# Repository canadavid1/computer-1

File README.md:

# computer-1
A repository containing documentation, specifications, images and code for my processor built out of discrete 2N7002  transistors.

## Motivation
This project is mostly intended as a learning experience. 

## Directories
### Kicad
Kicad files for all the PCBs used in the project.

NOTICE: some of these have some flaws. Do not rely on these working.
### Assembly
Assorted assembly programs, and the corresponding compiler.
### Emulator
Different levels of emulator for the system.
### Ideas
Ideas for further improvement or additions to the system.

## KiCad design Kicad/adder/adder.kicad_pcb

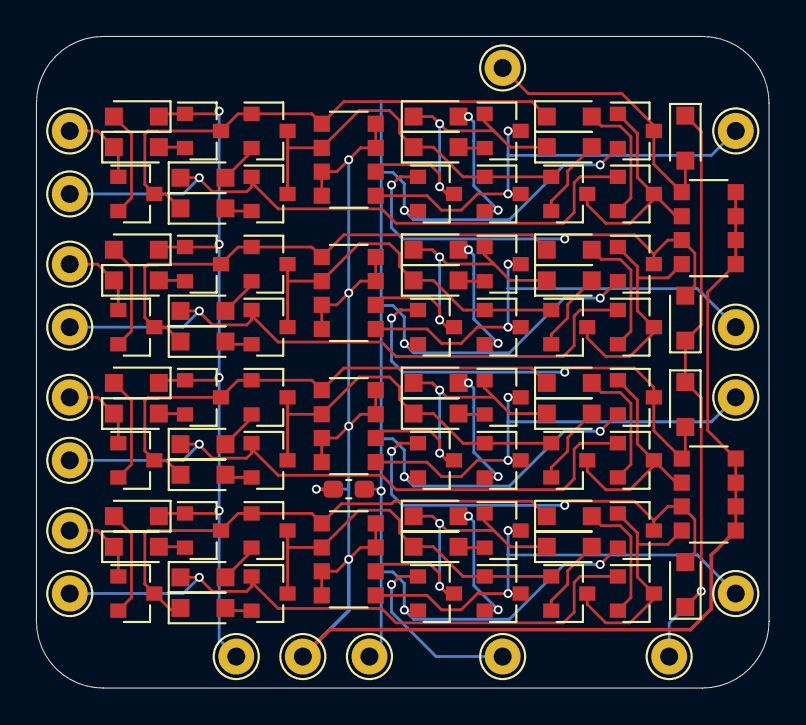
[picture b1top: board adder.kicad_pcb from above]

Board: 2 copper layers, 40.7 x 36.2 mm, 101 parts (0 on the bottom side), 69 nets.

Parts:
C0: C; C_0603_1608Metric_Pad1.08x0.95mm_HandSolder
D0, D1, D2, D3, D4, D5, D6, D7, D8, D201, D202, D203, D204, D205, D206, D207, D208, D209, D301, D302, D303, D304, D305, D306, D307, D308, D309, D401, D402, D403, D404, D405, D406, D407, D408, D409: D; D_SOD-323_HandSoldering
Q0, Q1, Q2, Q3, Q4, Q5, Q6, Q7, Q8, Q9, Q201, Q202, Q203, Q204, Q205, Q206, Q207, Q208, Q209, Q210, Q301, Q302, Q303, Q304, Q305, Q306, Q307, Q308, Q309, Q310, Q401, Q402, Q403, Q404, Q405, Q406, Q407, Q408, Q409, Q410: 2N7002; SOT-23
RN0, RN1, RN2, RN201, RN301, RN401: R_Pack04; R_Array_Convex_4x1206
TP0, TP1, TP2, TP3, TP4, TP5, TP6, TP7, TP8, TP201, TP202, TP203, TP301, TP302, TP303, TP401, TP402, TP403: Pin_D1.0mm_L10.0mm

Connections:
/1/A: D209.1, Q208.1, TP202.1
/1/B: D203.1, Q202.1, Q207.1, TP201.1
/1/SUM: Q204.3, Q205.3, RN201.5, TP203.1
/1/nA': D202.1, D207.1, Q203.1, Q208.3, Q209.3, RN201.1
/1/nCi: D205.1, D206.1, Q204.1, Q210.3, RN201.6
/1/nCo: Q201.1, Q206.3, Q207.3, RN1.2
/1/~A^B: D204.1, Q202.3, Q203.3, Q205.1, Q206.1, RN201.2
/2/A: D309.1, Q308.1, TP302.1
/2/B: D303.1, Q302.1, Q307.1, TP301.1
/2/Ci: D201.2, Q201.3, Q310.1, RN1.1
/2/SUM: Q304.3, Q305.3, RN301.5, TP303.1
/2/nA': D302.1, D307.1, Q303.1, Q308.3, Q309.3, RN301.1
/2/nCi: D305.1, D306.1, Q304.1, Q310.3, RN301.6
/2/nCo: Q301.1, Q306.3, Q307.3, RN2.4
/2/~A^B: D304.1, Q302.3, Q303.3, Q305.1, Q306.1, RN301.2
/3/A: D409.1, Q408.1, TP402.1
/3/B: D403.1, Q402.1, Q407.1, TP401.1
/3/Ci: D301.2, Q301.3, Q410.1, RN2.3
/3/Co: D401.2, Q401.3, RN2.1, TP5.1
/3/SUM: Q404.3, Q405.3, RN401.5, TP403.1
/3/nA': D402.1, D407.1, Q403.1, Q408.3, Q409.3, RN401.1
/3/nCi: D405.1, D406.1, Q404.1, Q410.3, RN401.6
/3/nCo: Q401.1, Q406.3, Q407.3, RN2.2
/3/~A^B: D404.1, Q402.3, Q403.3, Q405.1, Q406.1, RN401.2
/A: D8.1, Q7.1, TP2.1
/B: D2.1, Q1.1, Q6.1, TP1.1
/Ci: Q9.1, TP4.1
/Co: D0.2, Q0.3, Q210.1, RN1.3
/SUM: Q3.3, Q4.3, RN0.5, TP3.1
/nA': D1.1, D6.1, Q2.1, Q7.3, Q8.3, RN0.1
/nCi: D4.1, D5.1, Q3.1, Q9.3, RN0.6
/nCo: Q0.1, Q5.3, Q6.3, RN1.4
/~A^B: D3.1, Q1.3, Q2.3, Q4.1, Q5.1, RN0.2
CLRC: D0.1, D201.1, D301.1, D401.1, TP0.1
GND: C0.2, Q0.2, Q9.2, Q201.2, Q210.2, Q301.2, Q310.2, Q401.2, Q410.2, TP8.1
unnamed: D1.2, Q1.2
unnamed: D2.2, Q2.2
unnamed: D3.2, Q3.2
unnamed: D4.2, Q4.2
unnamed: D5.2, Q5.2
unnamed: D6.2, Q6.2
unnamed: D7.2, Q7.2
unnamed: D8.2, Q8.2
unnamed: D202.2, Q202.2
unnamed: D203.2, Q203.2
unnamed: D204.2, Q204.2
unnamed: D205.2, Q205.2
unnamed: D206.2, Q206.2
unnamed: D207.2, Q207.2
unnamed: D208.2, Q208.2
unnamed: D209.2, Q209.2
unnamed: D302.2, Q302.2
unnamed: D303.2, Q303.2
unnamed: D304.2, Q304.2
unnamed: D305.2, Q305.2
unnamed: D306.2, Q306.2
unnamed: D307.2, Q307.2
unnamed: D308.2, Q308.2
unnamed: D309.2, Q309.2
unnamed: D402.2, Q402.2
unnamed: D403.2, Q403.2
unnamed: D404.2, Q404.2
unnamed: D405.2, Q405.2
unnamed: D406.2, Q406.2
unnamed: D407.2, Q407.2
unnamed: D408.2, Q408.2
unnamed: D409.2, Q409.2
VCC: C0.1, RN0.3, RN0.4, RN0.7, RN0.8, RN1.5, RN1.6, RN1.7, RN1.8, RN2.5, RN2.6, RN2.7, RN2.8, RN201.3, RN201.4, RN201.7, RN201.8, RN301.3, RN301.4, RN301.7, RN301.8, RN401.3, RN401.4, RN401.7, RN401.8, TP7.1
~add: D7.1, D208.1, D308.1, D408.1, Q8.1, Q209.1, Q309.1, Q409.1, TP6.1

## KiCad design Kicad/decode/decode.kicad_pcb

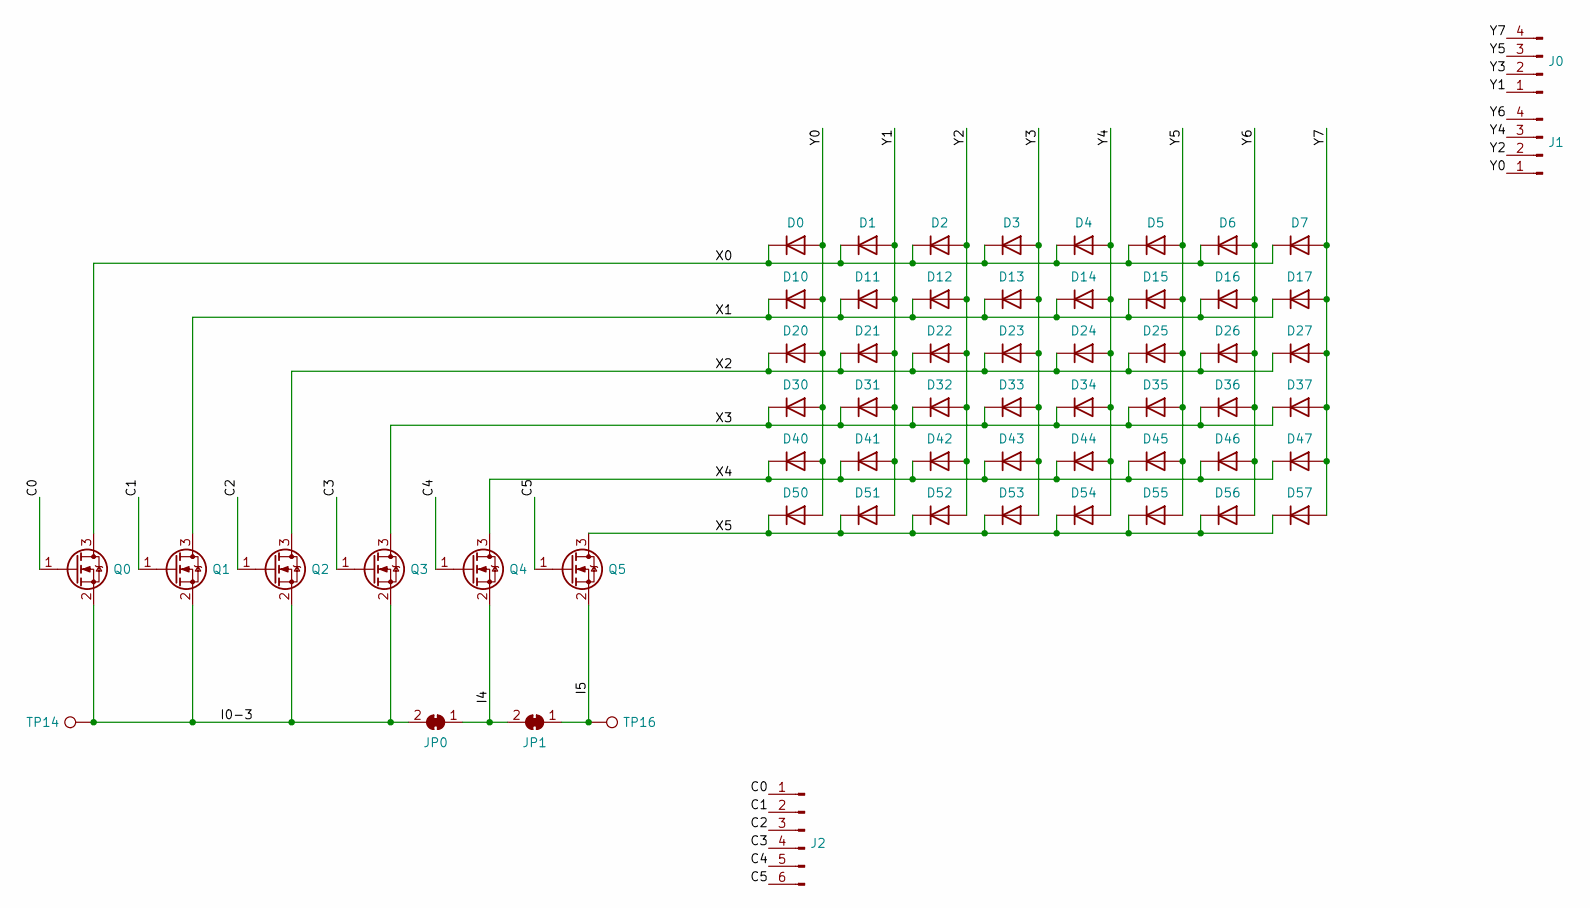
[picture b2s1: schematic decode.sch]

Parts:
D0, D1, D2, D3, D4, D5, D6, D7, D10, D11, D12, D13, D14, D15, D16, D17, D20, D21, D22, D23, D24, D25, D26, D27, D30, D31, D32, D33, D34, D35, D36, D37, D40, D41, D42, D43, D44, D45, D46, D47, D50, D51, D52, D53, D54, D55, D56, D57: D; D_SOD-323_HandSoldering
J0, J1: Conn_01x04_Male; PinHeader_1x04_P2.54mm_Vertical
J2: Conn_01x06_Male; PinHeader_1x06_P2.54mm_Vertical
JP0, JP1: SolderJumper_2_Bridged; SolderJumper-2_P1.3mm_Bridged_RoundedPad1.0x1.5mm
Q0, Q1, Q2, Q3, Q4, Q5: 2N7002; SOT-23
TP14, TP16: TestPoint; Pin_D1.0mm_L10.0mm

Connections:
/C0: J2.1, Q0.1 (G)
/C1: J2.2, Q1.1 (G)
/C2: J2.3, Q2.1 (G)
/C3: J2.4, Q3.1 (G)
/C4: J2.5, Q4.1 (G)
/C5: J2.6, Q5.1 (G)
/I0-3: JP0.2 (B), Q0.2 (S), Q1.2 (S), Q2.2 (S), Q3.2 (S), TP14.1
/I4: JP0.1 (A), JP1.2 (B), Q4.2 (S)
/I5: JP1.1 (A), Q5.2 (S), TP16.1
/X0: D0.1 (K), D1.1 (K), D2.1 (K), D3.1 (K), D4.1 (K), D5.1 (K), D6.1 (K), D7.1 (K), Q0.3 (D)
/X1: D10.1 (K), D11.1 (K), D12.1 (K), D13.1 (K), D14.1 (K), D15.1 (K), D16.1 (K), D17.1 (K), Q1.3 (D)
/X2: D20.1 (K), D21.1 (K), D22.1 (K), D23.1 (K), D24.1 (K), D25.1 (K), D26.1 (K), D27.1 (K), Q2.3 (D)
/X3: D30.1 (K), D31.1 (K), D32.1 (K), D33.1 (K), D34.1 (K), D35.1 (K), D36.1 (K), D37.1 (K), Q3.3 (D)
/X4: D40.1 (K), D41.1 (K), D42.1 (K), D43.1 (K), D44.1 (K), D45.1 (K), D46.1 (K), D47.1 (K), Q4.3 (D)
/X5: D50.1 (K), D51.1 (K), D52.1 (K), D53.1 (K), D54.1 (K), D55.1 (K), D56.1 (K), D57.1 (K), Q5.3 (D)
/Y0: D0.2 (A), D10.2 (A), D20.2 (A), D30.2 (A), D40.2 (A), D50.2 (A), J1.1
/Y1: D1.2 (A), D11.2 (A), D21.2 (A), D31.2 (A), D41.2 (A), D51.2 (A), J0.1
/Y2: D2.2 (A), D12.2 (A), D22.2 (A), D32.2 (A), D42.2 (A), D52.2 (A), J1.2
/Y3: D3.2 (A), D13.2 (A), D23.2 (A), D33.2 (A), D43.2 (A), D53.2 (A), J0.2
/Y4: D4.2 (A), D14.2 (A), D24.2 (A), D34.2 (A), D44.2 (A), D54.2 (A), J1.3
/Y5: D5.2 (A), D15.2 (A), D25.2 (A), D35.2 (A), D45.2 (A), D55.2 (A), J0.3
/Y6: D6.2 (A), D16.2 (A), D26.2 (A), D36.2 (A), D46.2 (A), D56.2 (A), J1.4
/Y7: D7.2 (A), D17.2 (A), D27.2 (A), D37.2 (A), D47.2 (A), D57.2 (A), J0.4

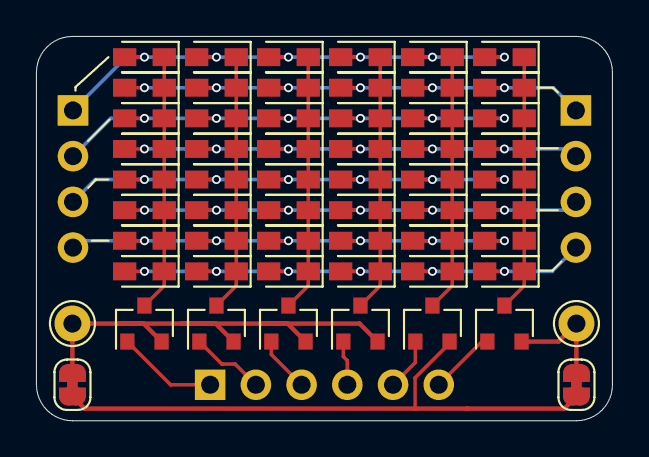
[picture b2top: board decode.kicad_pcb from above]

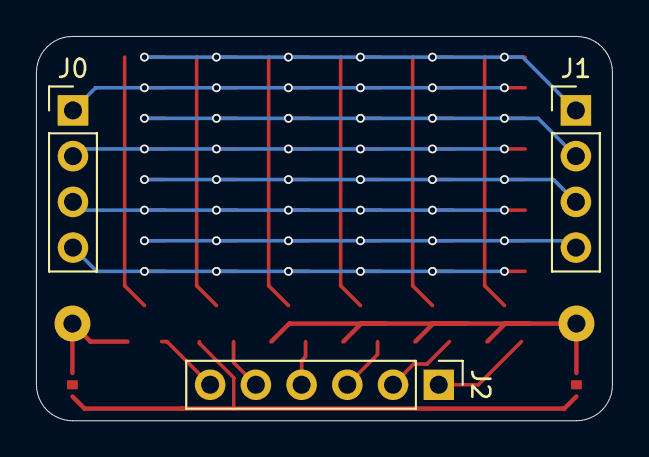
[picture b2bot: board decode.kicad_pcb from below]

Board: 2 copper layers, 32.0 x 21.3 mm, 61 parts (3 on the bottom side), 23 nets.

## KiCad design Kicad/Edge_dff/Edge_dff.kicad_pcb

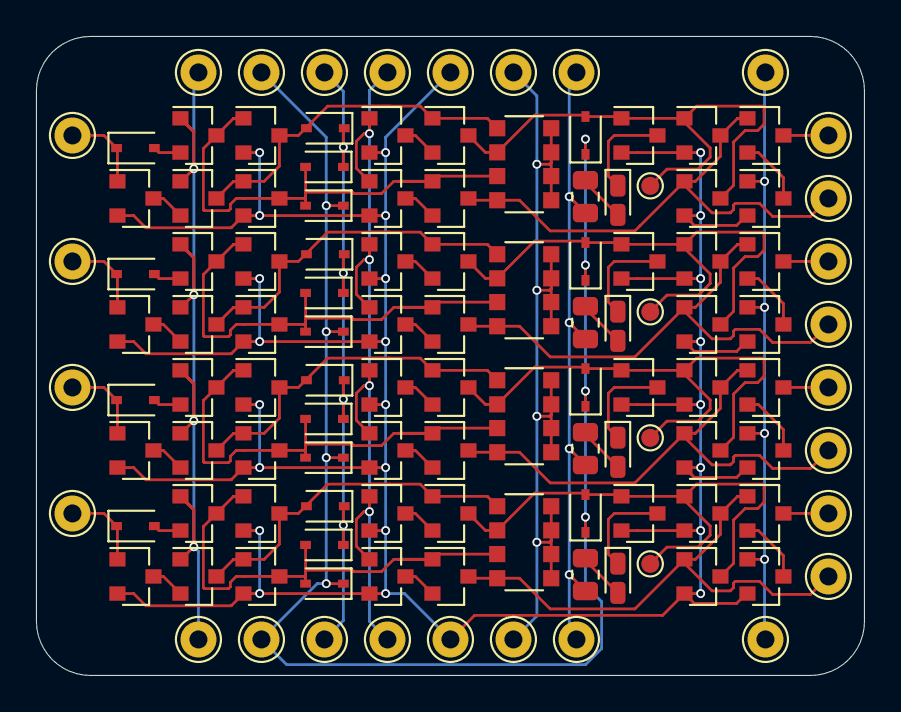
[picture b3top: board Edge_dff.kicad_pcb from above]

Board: 2 copper layers, 46.0 x 35.5 mm, 120 parts (0 on the bottom side), 60 nets.

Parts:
D201, D202, D203, D204, D205, D301, D302, D303, D304, D305, D401, D402, D403, D404, D405, D501, D502, D503, D504, D505: D; D_SOD-323
D206, D306, D406, D506: LED; LED_0603_1608Metric_Castellated
Q201, Q202, Q203, Q204, Q205, Q206, Q207, Q208, Q209, Q210, Q211, Q212, Q213, Q214, Q301, Q302, Q303, Q304, Q305, Q306, Q307, Q308, Q309, Q310, Q311, Q312, Q313, Q314, Q401, Q402, Q403, Q404, Q405, Q406, Q407, Q408, Q409, Q410, Q411, Q412, Q413, Q414, Q501, Q502, Q503, Q504, Q505, Q506, Q507, Q508, Q509, Q510, Q511, Q512, Q513, Q514: 2N7002; SOT-23
R201, R301, R401, R501: R; R_0805_2012Metric
RN201, RN301, RN401, RN501: R_Pack04; R_Array_Convex_4x1206
TP102, TP103, TP104, TP105, TP106, TP107, TP108, TP110, TP112, TP113, TP114, TP115, TP116, TP117, TP118, TP120, TP201, TP202, TP203, TP301, TP302, TP303, TP401, TP402, TP403, TP501, TP502, TP503: Pin_D1.0mm_L10.0mm
TP204, TP304, TP404, TP504: TestPoint_Pad_D1.0mm

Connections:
/one/B0: D301.1, Q303.1, TP301.1
/one/B0': Q313.3, TP302.1
/one/I0: D303.2, D304.2, Q301.3, Q304.1, Q305.3, Q306.1, RN301.3
/one/I0': D302.2, Q302.3, Q304.3, Q305.1, Q308.1, RN301.1
/one/Q0: D305.2, Q308.3, Q310.1, Q311.3, Q312.1, RN301.2, TP304.1
/one/Q0': Q306.3, Q310.3, Q311.1, Q313.1, RN301.4, TP303.1
/three/B0: D501.1, Q503.1, TP501.1
/three/B0': Q513.3, TP502.1
/three/I0: D503.2, D504.2, Q501.3, Q504.1, Q505.3, Q506.1, RN501.3
/three/I0': D502.2, Q502.3, Q504.3, Q505.1, Q508.1, RN501.1
/three/Q0: D505.2, Q508.3, Q510.1, Q511.3, Q512.1, RN501.2, TP504.1
/three/Q0': Q506.3, Q510.3, Q511.1, Q513.1, RN501.4, TP503.1
/two/B0: D401.1, Q403.1, TP401.1
/two/B0': Q413.3, TP402.1
/two/I0: D403.2, D404.2, Q401.3, Q404.1, Q405.3, Q406.1, RN401.3
/two/I0': D402.2, Q402.3, Q404.3, Q405.1, Q408.1, RN401.1
/two/Q0: D405.2, Q408.3, Q410.1, Q411.3, Q412.1, RN401.2, TP404.1
/two/Q0': Q406.3, Q410.3, Q411.1, Q413.1, RN401.4, TP403.1
/zero/B0: D201.1, Q203.1, TP201.1
/zero/B0': Q213.3, TP202.1
/zero/I0: D203.2, D204.2, Q201.3, Q204.1, Q205.3, Q206.1, RN201.3
/zero/I0': D202.2, Q202.3, Q204.3, Q205.1, Q208.1, RN201.1
/zero/Q0: D205.2, Q208.3, Q210.1, Q211.3, Q212.1, RN201.2, TP204.1
/zero/Q0': Q206.3, Q210.3, Q211.1, Q213.1, RN201.4, TP203.1
E: D202.1, D203.1, D302.1, D303.1, D402.1, D403.1, D502.1, D503.1, TP106.1, TP116.1
GND: Q203.2, Q204.2, Q205.2, Q207.2, Q209.2, Q210.2, Q211.2, Q212.2, Q214.2, Q303.2, Q304.2, Q305.2, Q307.2, Q309.2, Q310.2, Q311.2, Q312.2, Q314.2, Q403.2, Q404.2, Q405.2, Q407.2, Q409.2, Q410.2, Q411.2, Q412.2, Q414.2, Q503.2, Q504.2, Q505.2, Q507.2, Q509.2, Q510.2, Q511.2, Q512.2, Q514.2, TP110.1, TP120.1
unnamed: D201.2, Q201.2
unnamed: D206.1, Q212.3
unnamed: D206.2, R201.2
unnamed: D301.2, Q301.2
unnamed: D306.1, Q312.3
unnamed: D306.2, R301.2
unnamed: D401.2, Q401.2
unnamed: D406.1, Q412.3
unnamed: D406.2, R401.2
unnamed: D501.2, Q501.2
unnamed: D506.1, Q512.3
unnamed: D506.2, R501.2
unnamed: Q202.2, Q203.3
unnamed: Q206.2, Q207.3
unnamed: Q208.2, Q209.3
unnamed: Q213.2, Q214.3
unnamed: Q302.2, Q303.3
unnamed: Q306.2, Q307.3
unnamed: Q308.2, Q309.3
unnamed: Q313.2, Q314.3
unnamed: Q402.2, Q403.3
unnamed: Q406.2, Q407.3
unnamed: Q408.2, Q409.3
unnamed: Q413.2, Q414.3
unnamed: Q502.2, Q503.3
unnamed: Q506.2, Q507.3
unnamed: Q508.2, Q509.3
unnamed: Q513.2, Q514.3
VCC: RN201.5, RN201.6, RN201.7, RN201.8, RN301.5, RN301.6, RN301.7, RN301.8, RN401.5, RN401.6, RN401.7, RN401.8, RN501.5, RN501.6, RN501.7, RN501.8, TP108.1, TP118.1
Vdrive: R201.1, R301.1, R401.1, R501.1, TP107.1, TP117.1
phi1: Q201.1, Q202.1, Q301.1, Q302.1, Q401.1, Q402.1, Q501.1, Q502.1, TP104.1, TP114.1
phi2: Q207.1, Q209.1, Q307.1, Q309.1, Q407.1, Q409.1, Q507.1, Q509.1, TP103.1, TP113.1
~OE: Q214.1, Q314.1, Q414.1, Q514.1, TP102.1, TP112.1
~reset: D204.1, D205.1, D304.1, D305.1, D404.1, D405.1, D504.1, D505.1, TP105.1, TP115.1

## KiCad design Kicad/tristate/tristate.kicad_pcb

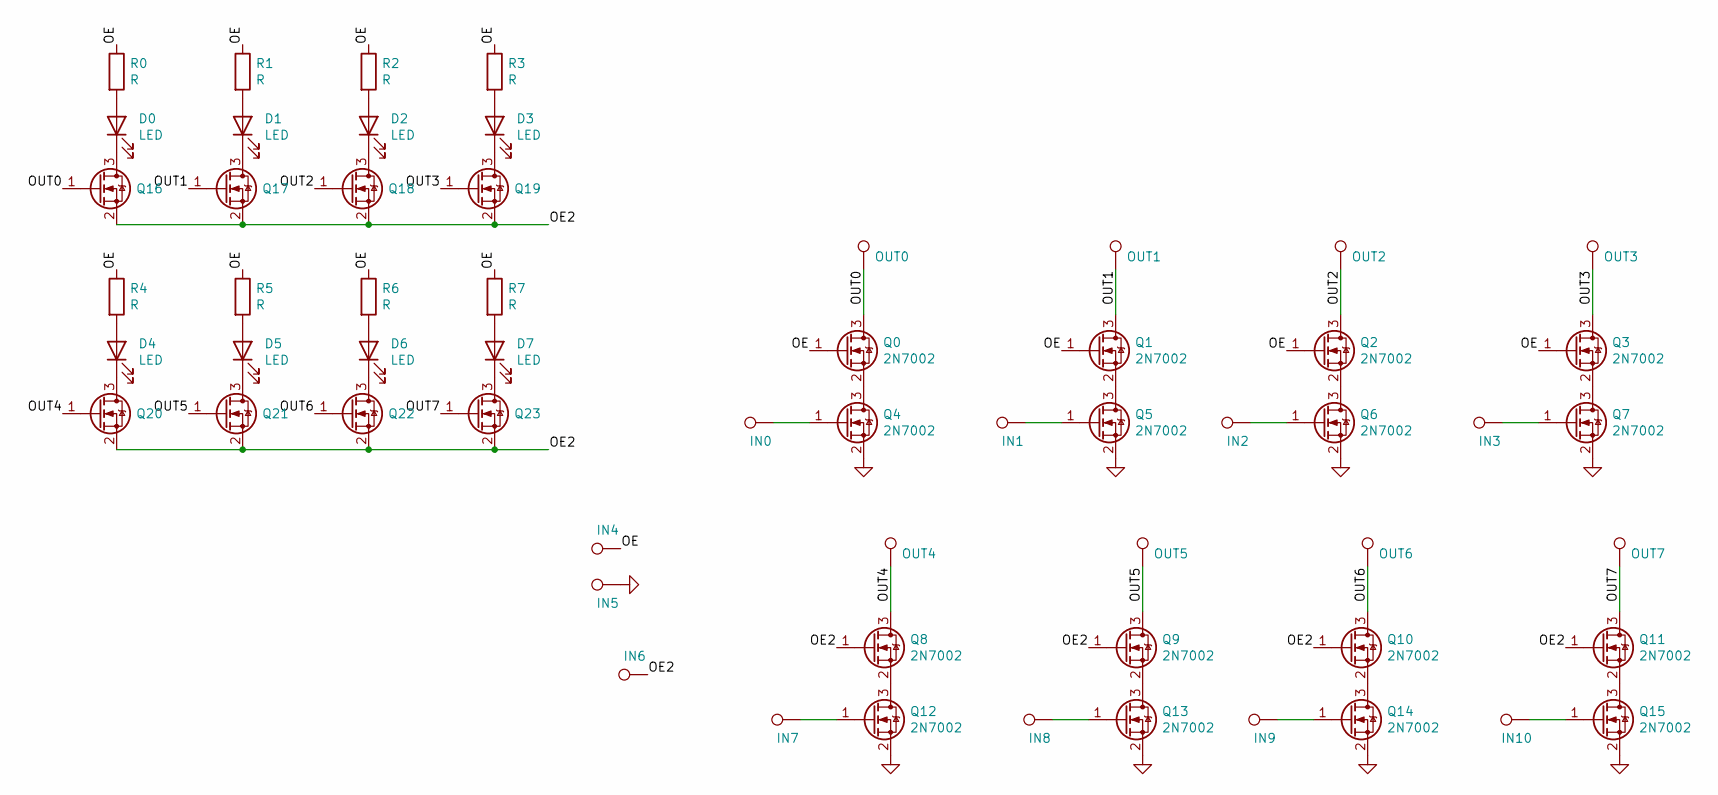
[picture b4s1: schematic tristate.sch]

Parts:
D0, D1, D2, D3, D4, D5, D6, D7: LED; LED_0603_1608Metric_Pad1.05x0.95mm_HandSolder
IN0, IN1, IN2, IN3, IN4, IN5, IN6, IN7, IN8, IN9, IN10: Pin_D1.0mm_L10.0mm
OUT0, OUT1, OUT2, OUT3, OUT4, OUT5, OUT6, OUT7: Pin_D1.0mm_L10.0mm
Q0, Q1, Q2, Q3, Q4, Q5, Q6, Q7, Q8, Q9, Q10, Q11, Q12, Q13, Q14, Q15, Q16, Q17, Q18, Q19, Q20, Q21, Q22, Q23: 2N7002; SOT-23
R0, R1, R2, R3, R4, R5, R6, R7: R; R_0603_1608Metric_Pad0.98x0.95mm_HandSolder

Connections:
/OE: IN4.1, Q0.1 (G), Q1.1 (G), Q2.1 (G), Q3.1 (G), R0.1, R1.1, R2.1, R3.1, R4.1, R5.1, R6.1, R7.1
/OE2: IN6.1, Q8.1 (G), Q9.1 (G), Q10.1 (G), Q11.1 (G), Q16.2 (S), Q17.2 (S), Q18.2 (S), Q19.2 (S), Q20.2 (S), Q21.2 (S), Q22.2 (S), Q23.2 (S)
/OUT0: OUT0.1, Q0.3 (D), Q16.1 (G)
/OUT1: OUT1.1, Q1.3 (D), Q17.1 (G)
/OUT2: OUT2.1, Q2.3 (D), Q18.1 (G)
/OUT3: OUT3.1, Q3.3 (D), Q19.1 (G)
/OUT4: OUT4.1, Q8.3 (D), Q20.1 (G)
/OUT5: OUT5.1, Q9.3 (D), Q21.1 (G)
/OUT6: OUT6.1, Q10.3 (D), Q22.1 (G)
/OUT7: OUT7.1, Q11.3 (D), Q23.1 (G)
GND: IN5.1, Q4.2 (S), Q5.2 (S), Q6.2 (S), Q7.2 (S), Q12.2 (S), Q13.2 (S), Q14.2 (S), Q15.2 (S)
unnamed: D0.1 (K), Q16.3 (D)
unnamed: D0.2 (A), R0.2
unnamed: D1.1 (K), Q17.3 (D)
unnamed: D1.2 (A), R1.2
unnamed: D2.1 (K), Q18.3 (D)
unnamed: D2.2 (A), R2.2
unnamed: D3.1 (K), Q19.3 (D)
unnamed: D3.2 (A), R3.2
unnamed: D4.1 (K), Q20.3 (D)
unnamed: D4.2 (A), R4.2
unnamed: D5.1 (K), Q21.3 (D)
unnamed: D5.2 (A), R5.2
unnamed: D6.1 (K), Q22.3 (D)
unnamed: D6.2 (A), R6.2
unnamed: D7.1 (K), Q23.3 (D)
unnamed: D7.2 (A), R7.2
unnamed: IN0.1, Q4.1 (G)
unnamed: IN1.1, Q5.1 (G)
unnamed: IN2.1, Q6.1 (G)
unnamed: IN3.1, Q7.1 (G)
unnamed: IN7.1, Q12.1 (G)
unnamed: IN8.1, Q13.1 (G)
unnamed: IN9.1, Q14.1 (G)
unnamed: IN10.1, Q15.1 (G)
unnamed: Q0.2 (S), Q4.3 (D)
unnamed: Q1.2 (S), Q5.3 (D)
unnamed: Q2.2 (S), Q6.3 (D)
unnamed: Q3.2 (S), Q7.3 (D)
unnamed: Q10.2 (S), Q14.3 (D)
unnamed: Q11.2 (S), Q15.3 (D)
unnamed: Q8.2 (S), Q12.3 (D)
unnamed: Q9.2 (S), Q13.3 (D)

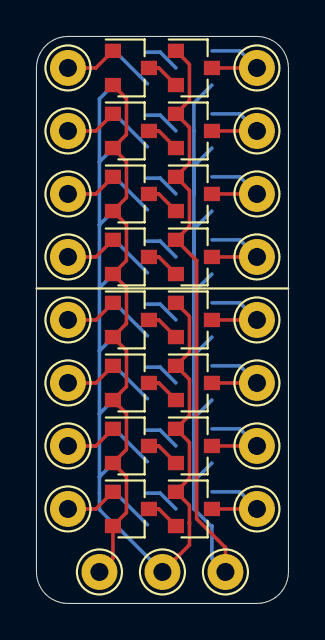
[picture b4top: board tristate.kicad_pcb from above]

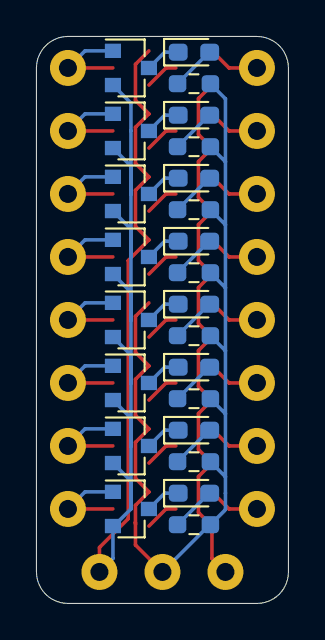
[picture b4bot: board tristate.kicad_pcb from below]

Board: 2 copper layers, 14.0 x 31.5 mm, 59 parts (24 on the bottom side), 43 nets.

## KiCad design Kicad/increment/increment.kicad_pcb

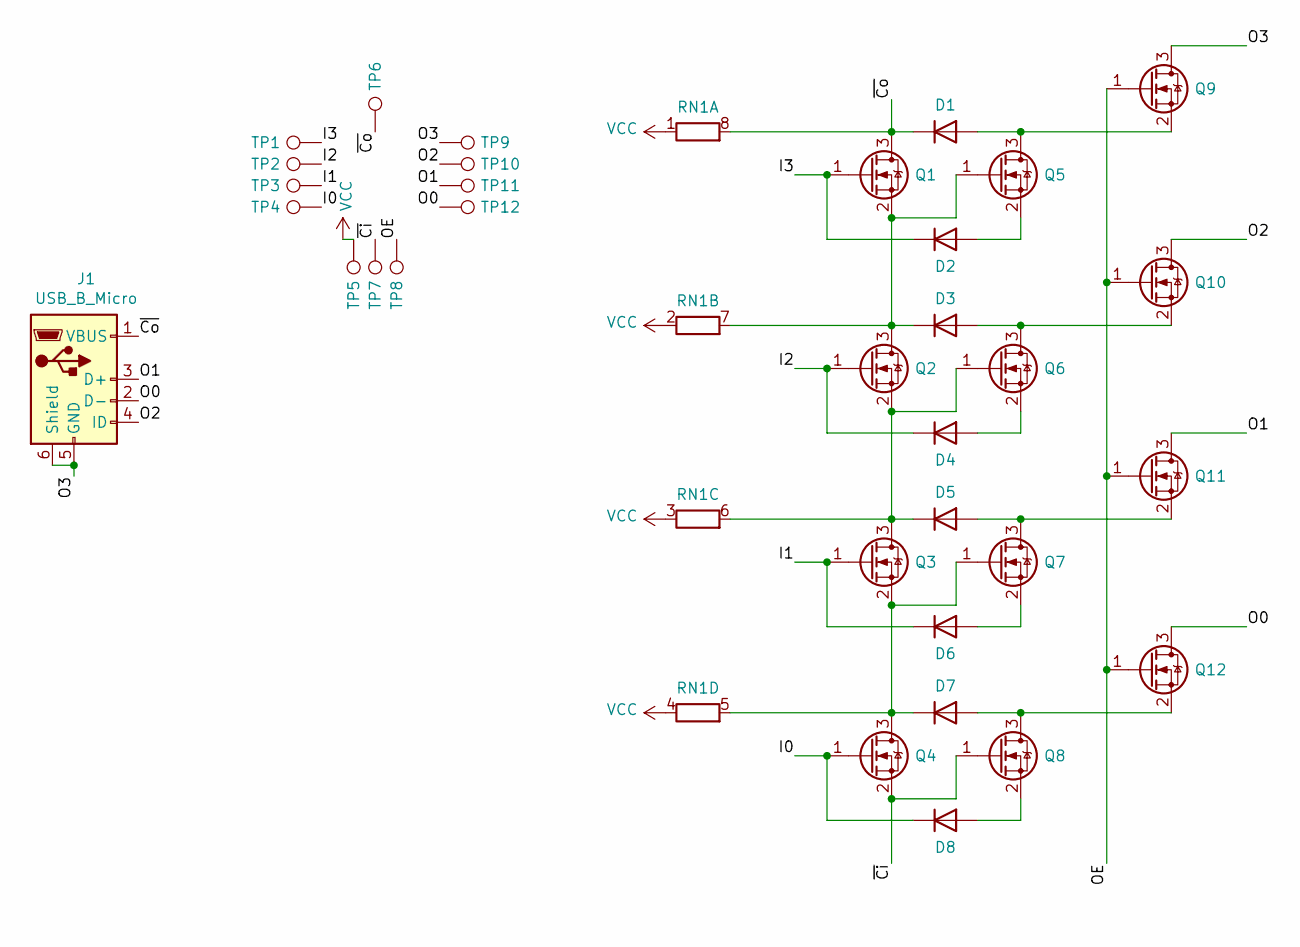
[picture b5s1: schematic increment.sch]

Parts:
D1, D2, D3, D4, D5, D6, D7, D8: D; D_SOD-323
J1: USB_B_Micro; USB_Micro-B_Amphenol_10104110_Horizontal
Q1, Q2, Q3, Q4, Q5, Q6, Q7, Q8, Q9, Q10, Q11, Q12: 2N7002; SOT-23
RN1: R_Pack04_Split; R_Array_Convex_4x1206
TP1, TP2, TP3, TP4, TP5, TP6, TP7, TP8, TP9, TP10, TP11, TP12: TestPoint; Pin_D1.0mm_L10.0mm

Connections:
/I0: D8.1 (K), Q4.1 (G), TP4.1
/I1: D6.1 (K), Q3.1 (G), TP3.1
/I2: D4.1 (K), Q2.1 (G), TP2.1
/I3: D2.1 (K), Q1.1 (G), TP1.1
/O0: J1.2 (D-), Q12.3 (D), TP12.1
/O1: J1.3 (D+), Q11.3 (D), TP11.1
/O2: J1.4 (ID), Q10.3 (D), TP10.1
/O3: J1.5 (GND), J1.6 (Shield), Q9.3 (D), TP9.1
/OE: Q9.1 (G), Q10.1 (G), Q11.1 (G), Q12.1 (G), TP8.1
/~Ci: Q4.2 (S), Q8.1 (G), TP7.1
/~Co: D1.1 (K), J1.1 (VBUS), Q1.3 (D), RN1.8 (R1.2), TP6.1
unnamed: D1.2 (A), Q5.3 (D), Q9.2 (S)
unnamed: D2.2 (A), Q5.2 (S)
unnamed: D3.1 (K), Q1.2 (S), Q2.3 (D), Q5.1 (G), RN1.7 (R2.2)
unnamed: D3.2 (A), Q6.3 (D), Q10.2 (S)
unnamed: D4.2 (A), Q6.2 (S)
unnamed: D5.1 (K), Q2.2 (S), Q3.3 (D), Q6.1 (G), RN1.6 (R3.2)
unnamed: D5.2 (A), Q7.3 (D), Q11.2 (S)
unnamed: D6.2 (A), Q7.2 (S)
unnamed: D7.1 (K), Q3.2 (S), Q4.3 (D), Q7.1 (G), RN1.5 (R4.2)
unnamed: D7.2 (A), Q8.3 (D), Q12.2 (S)
unnamed: D8.2 (A), Q8.2 (S)
VCC: RN1.1 (R1.1), RN1.2 (R2.1), RN1.3 (R3.1), RN1.4 (R4.1), TP5.1

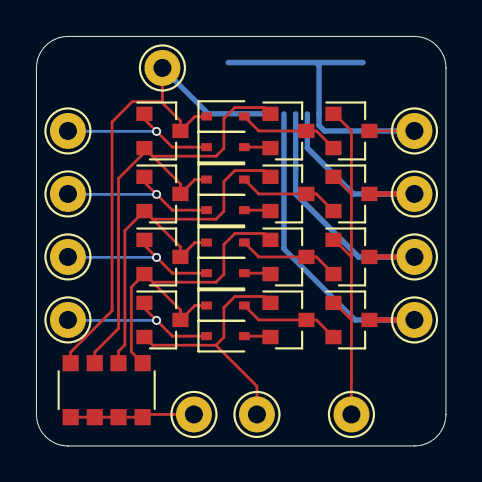
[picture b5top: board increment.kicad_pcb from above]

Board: 2 copper layers, 22.8 x 22.8 mm, 34 parts (1 on the bottom side), 23 nets.

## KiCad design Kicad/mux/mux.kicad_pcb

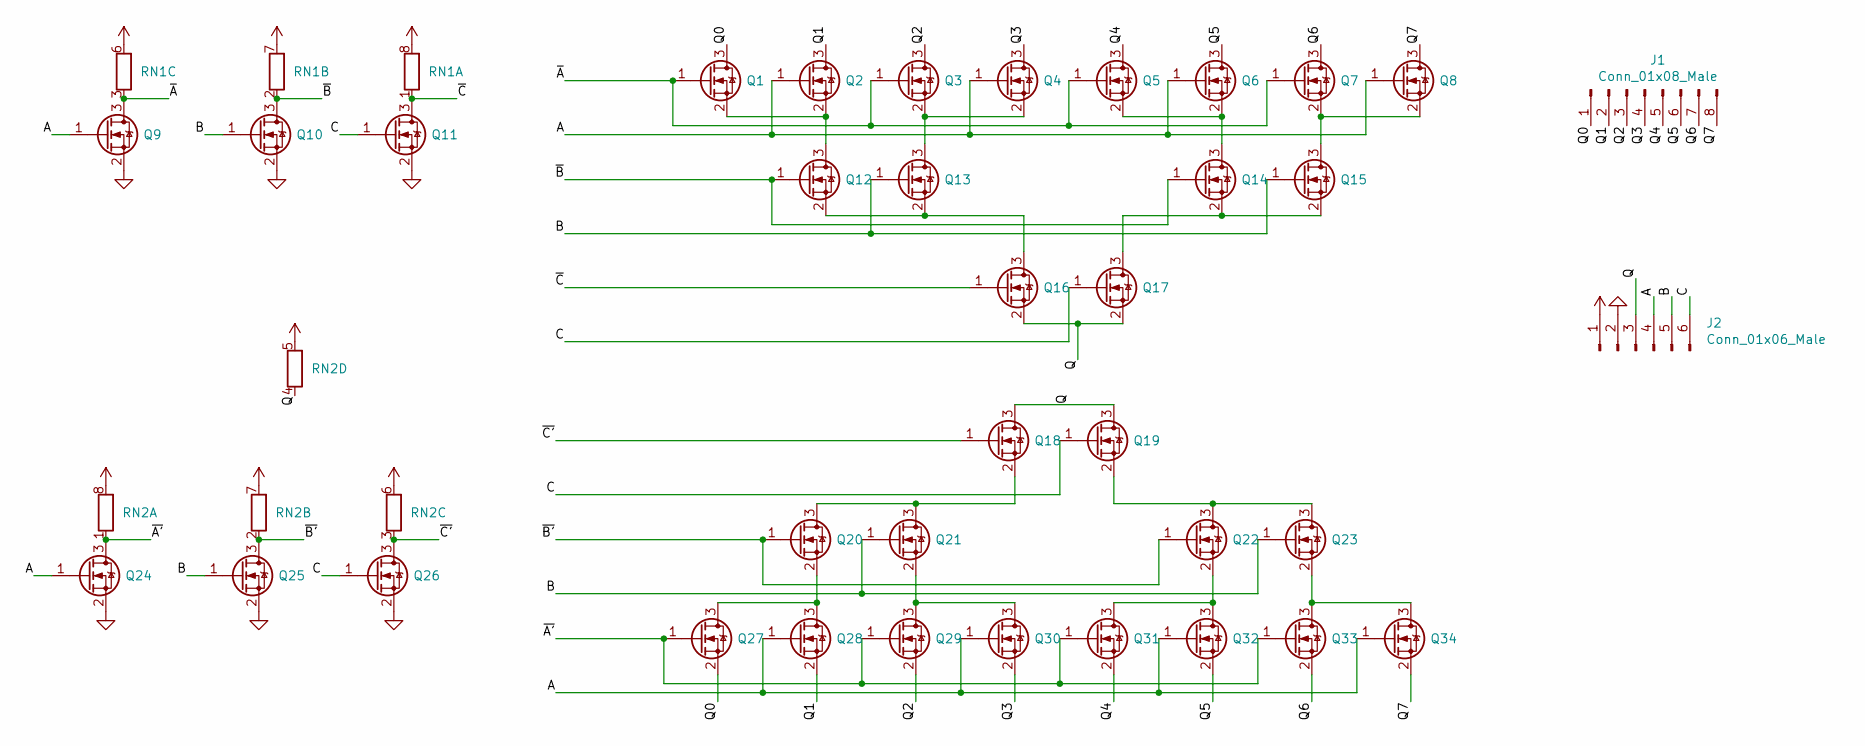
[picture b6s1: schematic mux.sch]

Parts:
J1: Conn_01x08_Male; PinHeader_1x08_P2.54mm_Vertical
J2: Conn_01x06_Male; PinHeader_1x06_P2.54mm_Vertical
Q1, Q2, Q3, Q4, Q5, Q6, Q7, Q8, Q9, Q10, Q11, Q12, Q13, Q14, Q15, Q16, Q17, Q18, Q19, Q20, Q21, Q22, Q23, Q24, Q25, Q26, Q27, Q28, Q29, Q30, Q31, Q32, Q33, Q34: 2N7002; SOT-23
RN1, RN2: R_Pack04_Split; R_Array_Convex_4x1206

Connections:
/A: J2.4, Q2.1 (G), Q4.1 (G), Q6.1 (G), Q8.1 (G), Q9.1 (G), Q24.1 (G), Q28.1 (G), Q30.1 (G), Q32.1 (G), Q34.1 (G)
/B: J2.5, Q10.1 (G), Q13.1 (G), Q15.1 (G), Q21.1 (G), Q23.1 (G), Q25.1 (G)
/C: J2.6, Q11.1 (G), Q17.1 (G), Q19.1 (G), Q26.1 (G)
/Q: J2.3, Q16.2 (S), Q17.2 (S), Q18.3 (D), Q19.3 (D), RN2.4 (R4.1)
/Q0: J1.1, Q1.3 (D), Q27.2 (S)
/Q1: J1.2, Q2.3 (D), Q28.2 (S)
/Q2: J1.3, Q3.3 (D), Q29.2 (S)
/Q3: J1.4, Q4.3 (D), Q30.2 (S)
/Q4: J1.5, Q5.3 (D), Q31.2 (S)
/Q5: J1.6, Q6.3 (D), Q32.2 (S)
/Q6: J1.7, Q7.3 (D), Q33.2 (S)
/Q7: J1.8, Q8.3 (D), Q34.2 (S)
/~A: Q1.1 (G), Q3.1 (G), Q5.1 (G), Q7.1 (G), Q9.3 (D), RN1.3 (R3.1)
/~A': Q24.3 (D), Q27.1 (G), Q29.1 (G), Q31.1 (G), Q33.1 (G), RN2.1 (R1.1)
/~B: Q10.3 (D), Q12.1 (G), Q14.1 (G), RN1.2 (R2.1)
/~B': Q20.1 (G), Q22.1 (G), Q25.3 (D), RN2.2 (R2.1)
/~C: Q11.3 (D), Q16.1 (G), RN1.1 (R1.1)
/~C': Q18.1 (G), Q26.3 (D), RN2.3 (R3.1)
GND: J2.2, Q9.2 (S), Q10.2 (S), Q11.2 (S), Q24.2 (S), Q25.2 (S), Q26.2 (S)
unnamed: Q1.2 (S), Q2.2 (S), Q12.3 (D)
unnamed: Q12.2 (S), Q13.2 (S), Q16.3 (D)
unnamed: Q3.2 (S), Q4.2 (S), Q13.3 (D)
unnamed: Q14.2 (S), Q15.2 (S), Q17.3 (D)
unnamed: Q5.2 (S), Q6.2 (S), Q14.3 (D)
unnamed: Q7.2 (S), Q8.2 (S), Q15.3 (D)
unnamed: Q18.2 (S), Q20.3 (D), Q21.3 (D)
unnamed: Q19.2 (S), Q22.3 (D), Q23.3 (D)
unnamed: Q20.2 (S), Q27.3 (D), Q28.3 (D)
unnamed: Q21.2 (S), Q29.3 (D), Q30.3 (D)
unnamed: Q22.2 (S), Q31.3 (D), Q32.3 (D)
unnamed: Q23.2 (S), Q33.3 (D), Q34.3 (D)
VCC: J2.1, RN1.6 (R3.2), RN1.7 (R2.2), RN1.8 (R1.2), RN2.5 (R4.2), RN2.6 (R3.2), RN2.7 (R2.2), RN2.8 (R1.2)

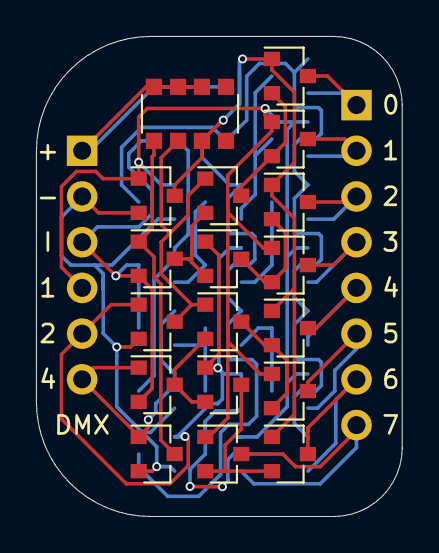
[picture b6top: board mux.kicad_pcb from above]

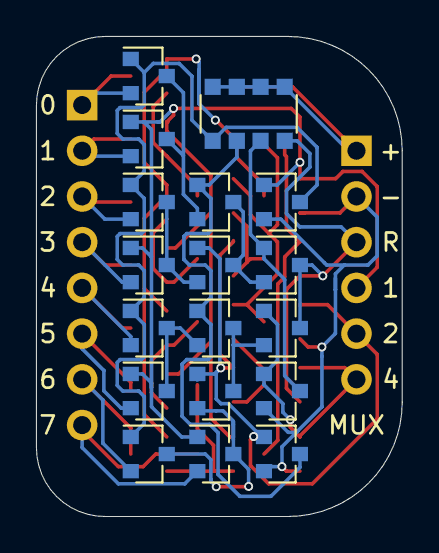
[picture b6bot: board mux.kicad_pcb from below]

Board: 2 copper layers, 20.3 x 26.7 mm, 38 parts (20 on the bottom side), 32 nets.

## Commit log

2023-02-14 Modified README.
2023-02-16 Added README for Assembly.
2023-02-16 Yes.
2023-02-23 Added Ideas.
2023-02-23 Fixed line spacings.
2023-02-23 changes.
2023-02-23 Added KICAD files.
